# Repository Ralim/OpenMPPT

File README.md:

# OpenMPPT
Open Source MPPT for Lithium Batteries. Based on TI controller

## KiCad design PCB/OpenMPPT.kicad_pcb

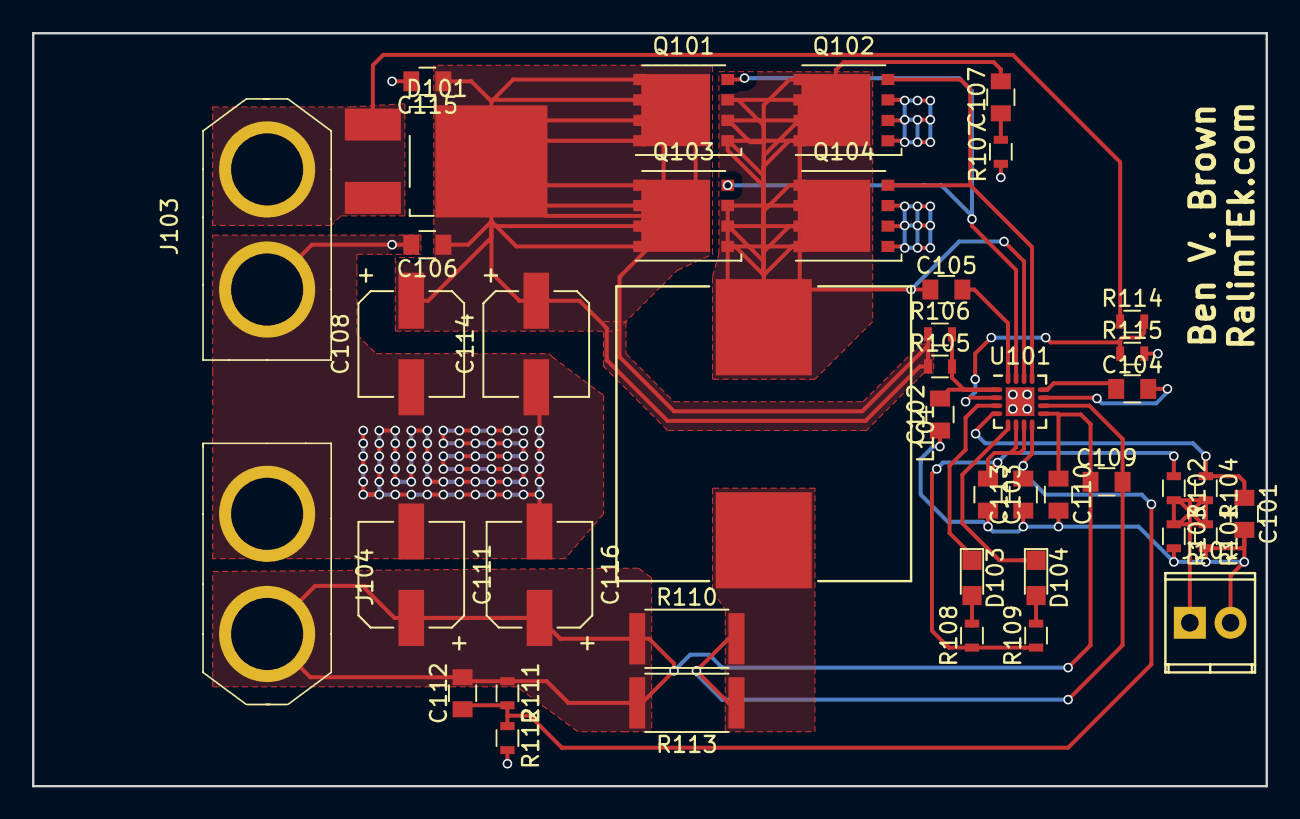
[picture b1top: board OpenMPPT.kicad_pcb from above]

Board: 2 copper layers, 77.0 x 47.0 mm, 43 parts (0 on the bottom side), 21 nets.

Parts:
C101, C107: -; C_0805
C102, C103, C106, C110, C115: 1.0uF; C_0805
C104, C105, C109, C112, C113: 0.1uF; C_0805
C108, C111, C114, C116: CP; CP_Elec_6.3x7.7
D101: MBRD10100CT; TO-252-2_Rectifier
D103, D104: LED; LED_0805
J101: THERM; TerminalBlock_Pheonix_MPT-2.54mm_2pol
J103, J104: XT60
L101: 3.3uH; Inductor_Wurth_HCI-1890
Q101, Q102, Q103, Q104: FDMS8050; TDSON-8-1
R101: 10k; R_0603
R102: 5.23k; R_0603
R103: 30.1k; R_0603
R104: 100; R_0603
R105, R106: 10; R_0603
R107: -; R_0603
R108, R109: R; R_0603
R110, R113: 0.010; R_2512
R111, R114: 499k; R_0603
R112: 100k; R_0603
R115: 36k; R_0603
U101: BQ24650; QFN-16-1EP_3x3mm_Pitch0.5mm

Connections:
/HIGH_DRIVE: Q101.4, Q103.4, U101.15
/LOW_DRIVE: Q102.4, Q104.4, U101.13
/MPPTSET: R114.2, R115.1, U101.2
/STAT1: D103.1, U101.3
/STAT2: D104.1, U101.5
/VREF: C103.1, R102.1, R108.1, R109.1, U101.6, U101.7
GND: C101.2, C102.1, C103.2, C104.2, C106.2, C108.2, C110.2, C111.2, C113.1, C114.2, C115.2, C116.2, J101.2, J103.2, J104.2, Q102.1, Q102.2, Q102.3, Q104.1, Q104.2, Q104.3, R101.2, R103.2, R107.1, R112.2, R115.2, U101.11, U101.17
unnamed: C101.1, R104.1, U101.4
unnamed: C102.2, R105.2, R106.2, U101.1
unnamed: C104.1, U101.12
unnamed: C105.1, C107.2, L101.1, Q101.1, Q101.2, Q101.3, Q102.5, Q103.1, Q103.2, Q103.3, Q104.5, U101.14
unnamed: C105.2, U101.16
unnamed: C106.1, C108.1, C114.1, C115.1, D101.2, Q101.5, Q103.5, R105.1, R106.1
unnamed: C107.1, R107.2
unnamed: C109.1, C110.1, C111.1, C112.2, C116.1, J104.1, R110.1, R111.1, R113.2, U101.9
unnamed: C109.2, L101.2, R110.2, R113.1, U101.10
unnamed: C112.1, C113.2, R111.2, R112.1, U101.8
unnamed: D101.1, D101.3, J103.1, R114.1
unnamed: D103.2, R108.2
unnamed: D104.2, R109.2
unnamed: J101.1, R101.1, R102.2, R103.1, R104.2

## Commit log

2017-05-27 Inital rough routing
2017-05-27 Add MPPT resistors
2017-07-08 Finish Routing
2017-07-08 Add schematic pdf
